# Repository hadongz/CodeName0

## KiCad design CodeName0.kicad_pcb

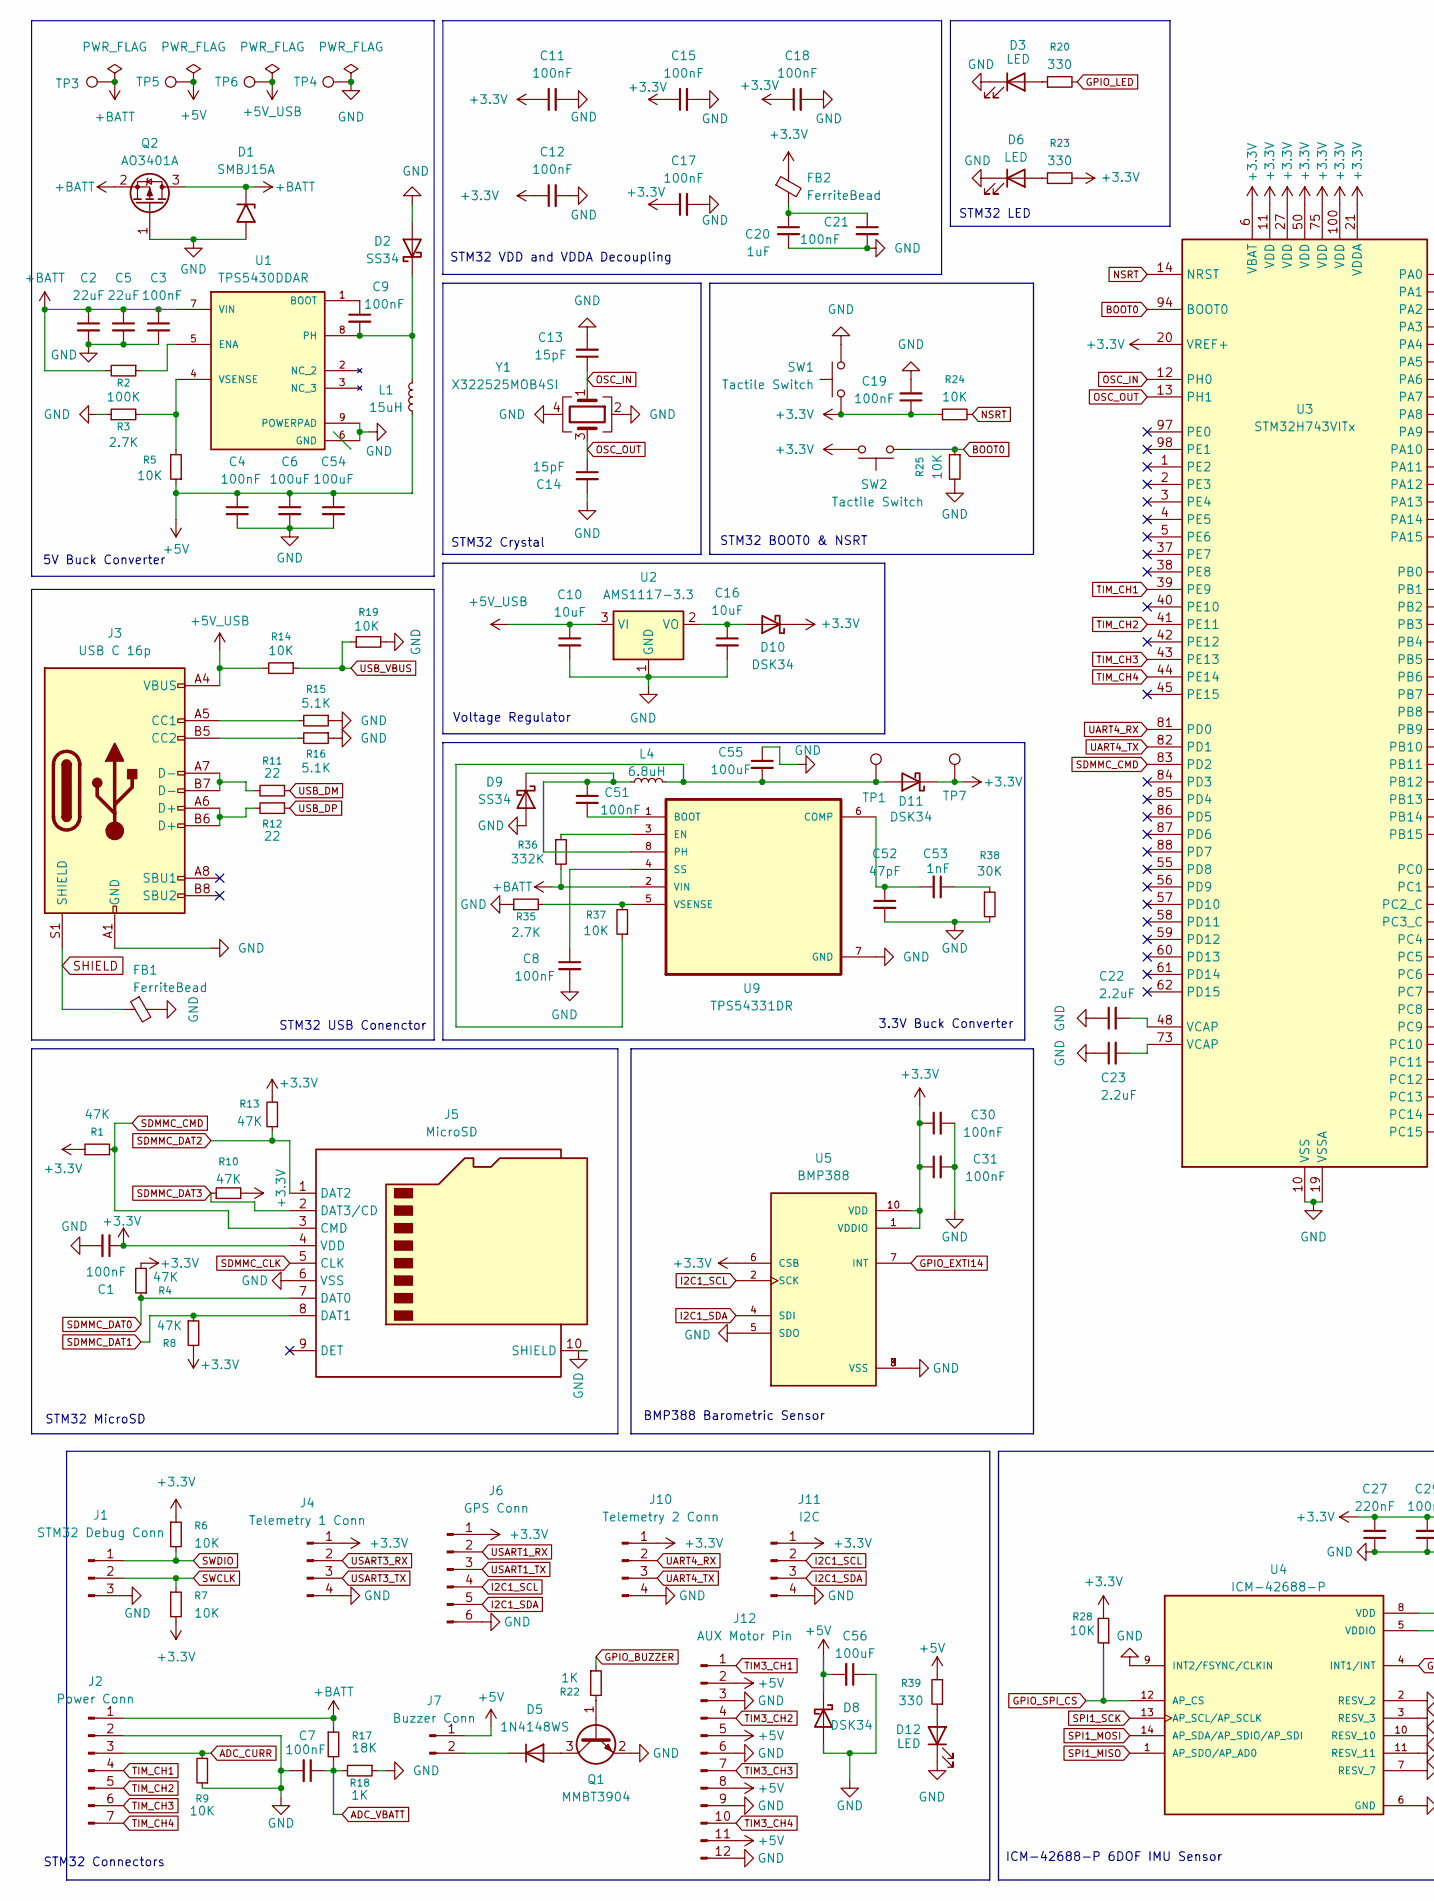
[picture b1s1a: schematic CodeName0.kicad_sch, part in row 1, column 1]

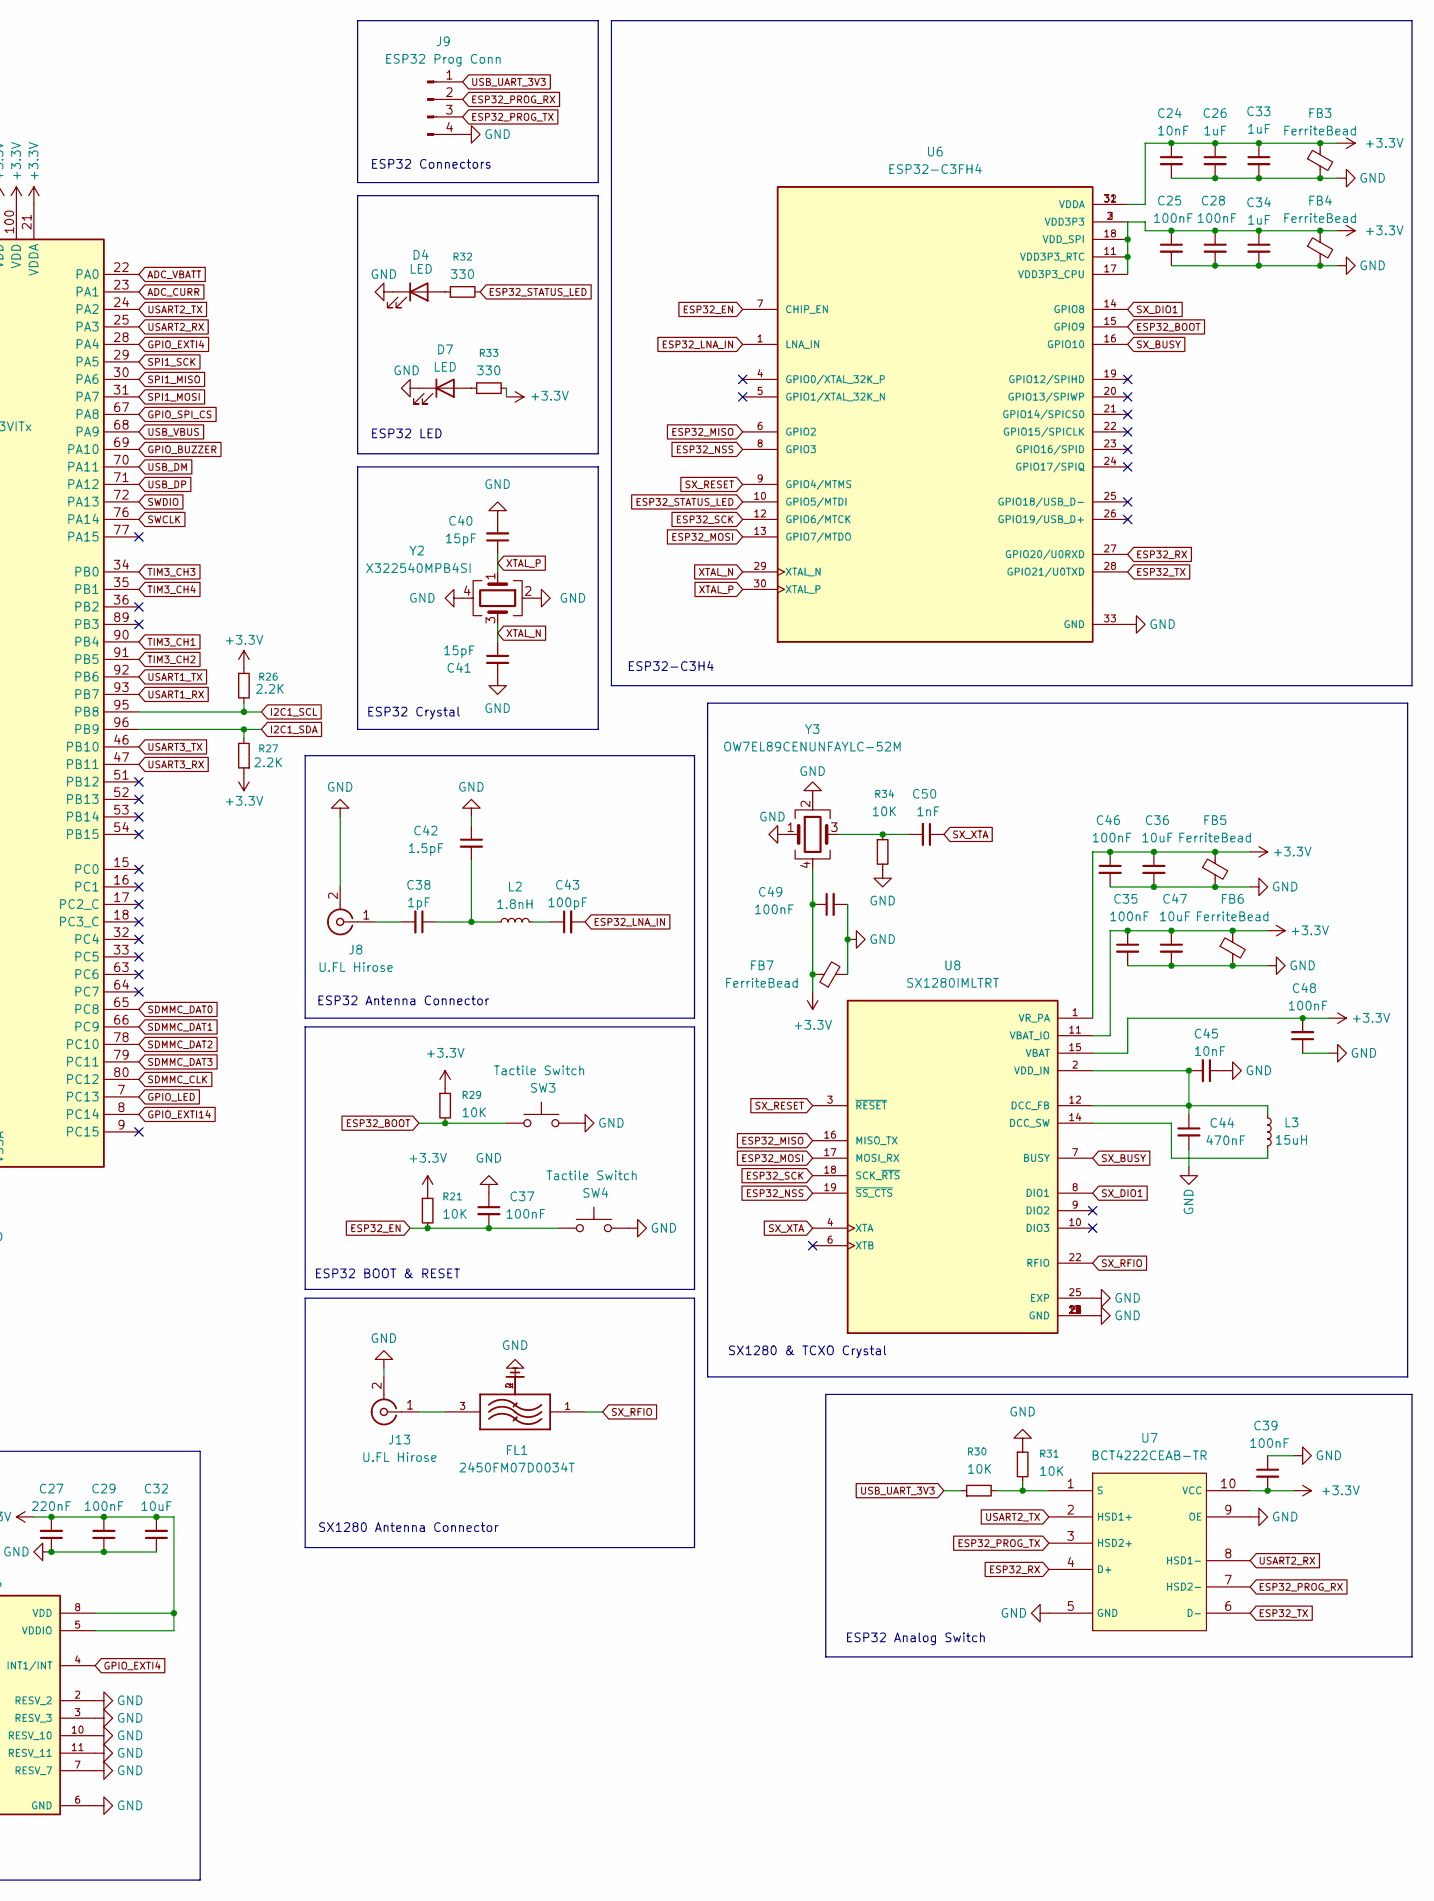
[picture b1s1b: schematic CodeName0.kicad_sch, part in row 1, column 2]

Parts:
C1, C3, C4, C7, C8, C9, C11, C12, C15, C17, C18, C19, C21, C25, C28, C29, C30, C31, C35, C37, C39, C46, C48, C49, C51: 100nF; C_0603_1608Metric
C2, C5: 22uF; C_1206_3216Metric
C6, C54, C55, C56: 100uF; C_1206_3216Metric
C10, C16, C32, C36, C47: 10uF; C_1206_3216Metric
C13, C14, C40, C41: 15pF; C_0603_1608Metric
C20: 1uF; C_0603_1608Metric
C22, C23: 2.2uF; C_0805_2012Metric
C24, C45: 10nF; C_0603_1608Metric
C26, C33, C34: 1uF; C_0805_2012Metric
C27: 220nF; C_0603_1608Metric
C38: 1pF; C_0402_1005Metric
C42: 1.5pF; C_0402_1005Metric
C43: 100pF; C_0402_1005Metric
C44: 470nF; C_0603_1608Metric
C50, C53: 1nF; C_0603_1608Metric
C52: 47pF; C_0402_1005Metric
D1: SMBJ15A; D_SMB
D2, D9: SS34; D_SMA
D3, D4: LED; LED_0805_2012Metric
D5: 1N4148WS; D_SOD-323
D6, D7, D12: LED; LED_0603_1608Metric
D8, D10, D11: DSK34; D_SOD-123F
FB1, FB2, FB3, FB4, FB5, FB6, FB7: FerriteBead; L_0603_1608Metric
FL1: 2450FM07D0034T; FIL_2450FM07D0034T; PARTREV 1.2
J1: STM32 Debug Conn; PinHeader_1x03_P2.54mm_Vertical
J2: Power Conn; JST_GH_SM07B-GHS-TB_1x07-1MP_P1.25mm_Horizontal
J3: USB C 16p; USB_C_Receptacle_HRO_TYPE-C-31-M-12
J4: Telemetry 1 Conn; JST_GH_SM04B-GHS-TB_1x04-1MP_P1.25mm_Horizontal
J5: MicroSD; SUNTECH_ST-TF-003A
J6: GPS Conn; JST_GH_SM06B-GHS-TB_1x06-1MP_P1.25mm_Horizontal
J7: Buzzer Conn; JST_GH_SM02B-GHS-TB_1x02-1MP_P1.25mm_Horizontal
J8, J13: U.FL Hirose; U.FL_Hirose_U.FL-R-SMT-1_Vertical
J9: ESP32 Prog Conn; PinHeader_1x04_P2.54mm_Vertical
J10: Telemetry 2 Conn; JST_GH_SM04B-GHS-TB_1x04-1MP_P1.25mm_Horizontal
J11: I2C; JST_GH_BM04B-GHS-TBT_1x04-1MP_P1.25mm_Vertical
J12: AUX Motor Pin; PinHeader_3x04_P2.54mm_Vertical
L1: 15uH; L_Bourns_SRP7028A_7.3x6.6mm
L2: 1.8nH; L_0402_1005Metric
L3: 15uH; L_Changjiang_FNR3015S
L4: 6.8uH; L_Sunlord_MWSA0503S
Q1: MMBT3904; SOT-23
Q2: AO3401A; SOT-23
R1, R4, R8, R10, R13: 47K; R_0603_1608Metric
R2: 100K; R_0603_1608Metric
R3, R35: 2.7K; R_0603_1608Metric
R5, R6, R7, R9, R14, R19, R21, R24, R25, R28, R29, R30, R31, R34, R37: 10K; R_0603_1608Metric
R11, R12: 22; R_0603_1608Metric
R15, R16: 5.1K; R_0603_1608Metric
R17: 18K; R_0603_1608Metric
R18, R22: 1K; R_0603_1608Metric
R20, R23, R32, R33, R39: 330; R_0603_1608Metric
R26, R27: 2.2K; R_0603_1608Metric
R36: 332K; R_0603_1608Metric
R38: 30K; R_0603_1608Metric
SW1, SW2, SW3, SW4: Tactile Switch; SW_Push_SPST_NO_Alps_SKRK
TP1, TP3, TP5, TP6, TP7: TestPoint; TestPoint_Pad_D1.5mm
TP4: TestPoint; TestPoint_Pad_D2.5mm
U1: TPS5430DDAR; CONV_TPS5430DDAR; PARTREV I
U2: AMS1117-3.3; SOT-223-3_TabPin2
U3: STM32H743VITx; LQFP-100_14x14mm_P0.5mm
U4: ICM-42688-P; PQFN50P300X250X97-14N; PARTREV 1.2
U5: BMP388; PQFN50P200X200X80-10N; PARTREV 1.1
U6: ESP32-C3FH4; QFN50P500X500X90-33N; PARTREV 2.0
U7: BCT4222CEAB-TR; MSOP-10_3x3mm_P0.5mm
U8: SX1280IMLTRT; XCVR_SX1280IMLTRT; PARTREV 3.3
U9: TPS54331DR; SOIC127P599X175-8N
Y1: X322525MOB4SI; Crystal_SMD_3225-4Pin_3.2x2.5mm
Y2: X322540MPB4SI; Crystal_SMD_3225-4Pin_3.2x2.5mm
Y3: OW7EL89CENUNFAYLC-52M; Crystal_SMD_2016-4Pin_2.0x1.6mm

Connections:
+3.3V: C1.1, C11.1, C12.1, C15.1, C17.1, C18.1, C19.1, C24.1, C25.1, C26.1, C27.2, C28.1, C29.2, C30.1, C31.1, C32.2, C33.1, C34.1, C35.1, C36.1, C39.2, C46.1, C47.1, C48.2, C49.1, D10.1 (K), D11.1 (K), FB2.1, FB3.1, FB4.1, FB5.1, FB6.1, FB7.1, J4.1, J5.4 (VDD), J6.1, J10.1, J11.1, R1.1, R4.2, R6.1, R7.2, R8.2, R10.2, R13.2, R21.1, R23.2, R24.1, R26.1, R27.1, R28.2, R29.1, R33.2, SW1.2, SW2.1, TP7.1, U3.6 (VBAT), U3.11 (VDD), U3.20 (VREF+), U3.21 (VDDA), U3.27 (VDD), U3.50 (VDD), U3.75 (VDD), U3.100 (VDD), U4.5 (VDDIO), U4.8 (VDD), U5.1 (VDDIO), U5.6 (CSB), U5.10 (VDD), U6.2 (VDD3P3), U6.3 (VDD3P3), U6.11 (VDD3P3_RTC), U6.17 (VDD3P3_CPU), U6.18 (VDD_SPI), U6.31 (VDDA), U6.32 (VDDA), U7.10 (VCC), U8.1 (VR_PA), U8.11 (VBAT_IO), U8.15 (VBAT), Y3.4
+5V: C4.1, C6.1, C54.1, C56.2, D8.1 (K), J7.1, J12.2, J12.5, J12.8, J12.11, L1.1, R5.1, R39.2, TP5.1
+5V_USB: C10.1, J3.A4 (VBUS), J3.A9 (VBUS), J3.B4 (VBUS), J3.B9 (VBUS), R14.2, TP6.1, U2.3 (VI)
+BATT: C2.1, C3.1, C5.1, D1.1 (A1), J2.1, Q2.2 (S), Q2.3 (D), R2.2, R17.1, R36.2, TP3.1, U1.7 (VIN), U9.2 (VIN)
ADC_CURR: J2.3, R9.2, U3.23 (PA1)
ADC_VBATT: C7.1, R17.2, R18.2, U3.22 (PA0)
BOOT0: R25.1, SW2.2, U3.94 (BOOT0)
ESP32_BOOT: R29.2, SW3.2, U6.15 (GPIO9)
ESP32_EN: C37.2, R21.2, SW4.2, U6.7 (CHIP_EN)
ESP32_LNA_IN: C43.2, U6.1 (LNA_IN)
ESP32_MISO: U6.6 (GPIO2), U8.16 (MISO_TX)
ESP32_MOSI: U6.13 (GPIO7/MTDO), U8.17 (MOSI_RX)
ESP32_NSS: U6.8 (GPIO3), U8.19 (~SS_CTS)
ESP32_PROG_RX: J9.2, U7.7 (HSD2-)
ESP32_PROG_TX: J9.3, U7.3 (HSD2+)
ESP32_RX: U6.27 (GPIO20/U0RXD), U7.4 (D+)
ESP32_SCK: U6.12 (GPIO6/MTCK), U8.18 (SCK_~RTS)
ESP32_STATUS_LED: R32.2, U6.10 (GPIO5/MTDI)
ESP32_TX: U6.28 (GPIO21/U0TXD), U7.6 (D-)
GND: C1.2, C2.2, C3.2, C4.2, C5.2, C6.2, C7.2, C8.2, C10.2, C11.2, C12.2, C13.2, C14.2, C15.2, C16.2, C17.2, C18.2, C19.2, C20.2, C21.2, C22.1, C23.1, C24.2, C25.2, C26.2, C27.1, C28.2, C29.1, C30.2, C31.2, C32.1, C33.2, C34.2, C35.2, C36.2, C37.1, C39.1, C40.2, C41.2, C42.1, C44.2, C45.1, C46.2, C47.2, C48.1, C49.2, C52.2, C54.2, C55.1, C56.1, D1.2 (A2), D2.2 (A), D3.1 (K), D4.1 (K), D6.1 (K), D7.1 (K), D8.2 (A), D9.2 (A), D12.1 (K), FB1.2, FB3.2, FB4.2, FB5.2, FB6.2, FB7.2, FL1.2, FL1.4, J1.3, J2.2, J2.MP, J3.A1 (GND), J3.A12 (GND), J3.B1 (GND), J3.B12 (GND), J4.4, J4.MP, J5.6 (VSS), J5.10 (SHIELD), J6.6, J6.MP, J7.MP, J8.2 (Ext), J9.4, J10.4, J10.MP, J11.4, J11.MP, J12.3, J12.6, J12.9, J12.12, J13.2 (Ext), Q1.2 (E), Q2.1 (G), R3.1, R9.1, R15.1, R16.1, R18.1, R19.2, R25.2, R31.1, R34.2, R35.1, R38.2, SW1.1, SW3.1, SW4.1, TP4.1, U1.6 (GND), U1.9 (POWERPAD), U2.1 (GND), U3.10 (VSS), U3.19 (VSSA), U3.26 (VSS), U3.49 (VSS), U3.74 (VSS), U3.99 (VSS), U4.2 (RESV_2), U4.3 (RESV_3), U4.6 (GND), U4.7 (RESV_7), U4.9 (INT2/FSYNC/CLKIN), U4.10 (RESV_10), U4.11 (RESV_11), U5.3 (VSS), U5.5 (SDO), U5.8 (VSS), U5.9 (VSS), U6.33 (GND), U7.5 (GND), U7.9 (OE), U8.5 (GND), U8.13 (GND), U8.20 (GND), U8.21 (GND), U8.23 (GND), U8.24 (GND), U8.25 (EXP), U9.7 (GND), Y1.2, Y1.4, Y2.2, Y2.4, Y3.1, Y3.2
GPIO_BUZZER: R22.1, U3.69 (PA10)
GPIO_EXTI4: U3.28 (PA4), U4.4 (INT1/INT)
GPIO_EXTI14: U3.8 (PC14), U5.7 (INT)
GPIO_LED: R20.2, U3.7 (PC13)
GPIO_SPI_CS: R28.1, U3.67 (PA8), U4.12 (AP_CS)
I2C1_SCL: J6.4, J11.2, R26.2, U3.95 (PB8), U5.2 (SCK)
I2C1_SDA: J6.5, J11.3, R27.2, U3.96 (PB9), U5.4 (SDI)
NSRT: R24.2, U3.14 (NRST)
unnamed: C20.1, C21.1, FB2.2
unnamed: C22.2, U3.48 (VCAP)
unnamed: C23.2, U3.73 (VCAP)
unnamed: C38.1, C42.2, L2.1
unnamed: C43.1, L2.2
unnamed: C50.2, R34.1, Y3.3
unnamed: C53.1, R38.1
unnamed: C9.2, D2.1 (K), L1.2, U1.8 (PH)
unnamed: D3.2 (A), R20.1
unnamed: D4.2 (A), R32.1
unnamed: D5.2 (A), Q1.3 (C)
unnamed: D5.1 (K), J7.2
unnamed: D6.2 (A), R23.1
unnamed: D7.2 (A), R33.1
unnamed: C51.1, D9.1 (K), L4.1, U9.8 (PH)
unnamed: C16.1, D10.2 (A), U2.2 (VO)
unnamed: C55.2, D11.2 (A), L4.2, R37.1, TP1.1
unnamed: D12.2 (A), R39.1
unnamed: J3.A5 (CC1), R15.2
unnamed: J3.B5 (CC2), R16.2
unnamed: J3.A6 (D+), J3.B6 (D+), R12.2
unnamed: J3.A7 (D-), J3.B7 (D-), R11.2
unnamed: C38.2, J8.1 (In)
unnamed: FL1.3, J13.1 (In)
unnamed: Q1.1 (B), R22.2
unnamed: C9.1, U1.1 (BOOT)
unnamed: R2.1, U1.5 (ENA)
unnamed: R3.2, R5.2, U1.4 (VSENSE)
unnamed: R30.2, R31.2, U7.1 (S)
unnamed: C44.1, C45.2, L3.1, U8.2 (VDD_IN), U8.12 (DCC_FB)
unnamed: L3.2, U8.14 (DCC_SW)
unnamed: C51.2, U9.1 (BOOT)
unnamed: C52.1, C53.2, U9.6 (COMP)
unnamed: R36.1, U9.3 (EN)
unnamed: C8.1, U9.4 (SS)
unnamed: R35.2, R37.2, U9.5 (VSENSE)
OSC_IN: C13.1, U3.12 (PH0), Y1.1
OSC_OUT: C14.1, U3.13 (PH1), Y1.3
SDMMC_CLK: J5.5 (CLK), U3.80 (PC12)
SDMMC_CMD: J5.3 (CMD), R1.2, U3.83 (PD2)
SDMMC_DAT0: J5.7 (DAT0), R4.1, U3.65 (PC8)
SDMMC_DAT1: J5.8 (DAT1), R8.1, U3.66 (PC9)
SDMMC_DAT2: J5.1 (DAT2), R13.1, U3.78 (PC10)
SDMMC_DAT3: J5.2 (DAT3/CD), R10.1, U3.79 (PC11)
SHIELD: FB1.1, J3.S1 (SHIELD)
SPI1_MISO: U3.30 (PA6), U4.1 (AP_SDO/AP_AD0)
SPI1_MOSI: U3.31 (PA7), U4.14 (AP_SDA/AP_SDIO/AP_SDI)
SPI1_SCK: U3.29 (PA5), U4.13 (AP_SCL/AP_SCLK)
SWCLK: J1.2, R7.1, U3.76 (PA14)
SWDIO: J1.1, R6.2, U3.72 (PA13)
SX_BUSY: U6.16 (GPIO10), U8.7 (BUSY)
SX_DIO1: U6.14 (GPIO8), U8.8 (DIO1)
SX_RESET: U6.9 (GPIO4/MTMS), U8.3 (~RESET)
SX_RFIO: FL1.1, U8.22 (RFIO)
SX_XTA: C50.1, U8.4 (XTA)
TIM3_CH1: J12.1, U3.90 (PB4)
TIM3_CH2: J12.4, U3.91 (PB5)
TIM3_CH3: J12.7, U3.34 (PB0)
TIM3_CH4: J12.10, U3.35 (PB1)
TIM_CH1: J2.4, U3.39 (PE9)
TIM_CH2: J2.5, U3.41 (PE11)
TIM_CH3: J2.6, U3.43 (PE13)
TIM_CH4: J2.7, U3.44 (PE14)
UART4_RX: J10.2, U3.81 (PD0)
UART4_TX: J10.3, U3.82 (PD1)
USART1_RX: J6.2, U3.93 (PB7)
USART1_TX: J6.3, U3.92 (PB6)
USART2_RX: U3.25 (PA3), U7.8 (HSD1-)
USART2_TX: U3.24 (PA2), U7.2 (HSD1+)
USART3_RX: J4.2, U3.47 (PB11)
USART3_TX: J4.3, U3.46 (PB10)
USB_DM: R11.1, U3.70 (PA11)
USB_DP: R12.1, U3.71 (PA12)
USB_UART_3V3: J9.1, R30.1
USB_VBUS: R14.1, R19.1, U3.68 (PA9)
XTAL_N: C41.1, U6.29 (XTAL_N), Y2.3
XTAL_P: C40.1, U6.30 (XTAL_P), Y2.1

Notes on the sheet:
STM32 Crystal
ESP32 Connectors
ESP32-C3H4
SX1280 & TCXO Crystal
STM32 LED
STM32 BOOT0 & NSRT
ESP32 Analog Switch
STM32 VDD and VDDA Decoupling
STM32 USB Conenctor
STM32 Connectors
SX1280 Antenna Connector
STM32 MicroSD
BMP388 Barometric Sensor
ICM-42688-P 6DOF IMU Sensor
ESP32 LED
ESP32 Antenna Connector
3.3V Buck Converter
Voltage Regulator
5V Buck Converter
ESP32 Crystal
ESP32 BOOT & RESET

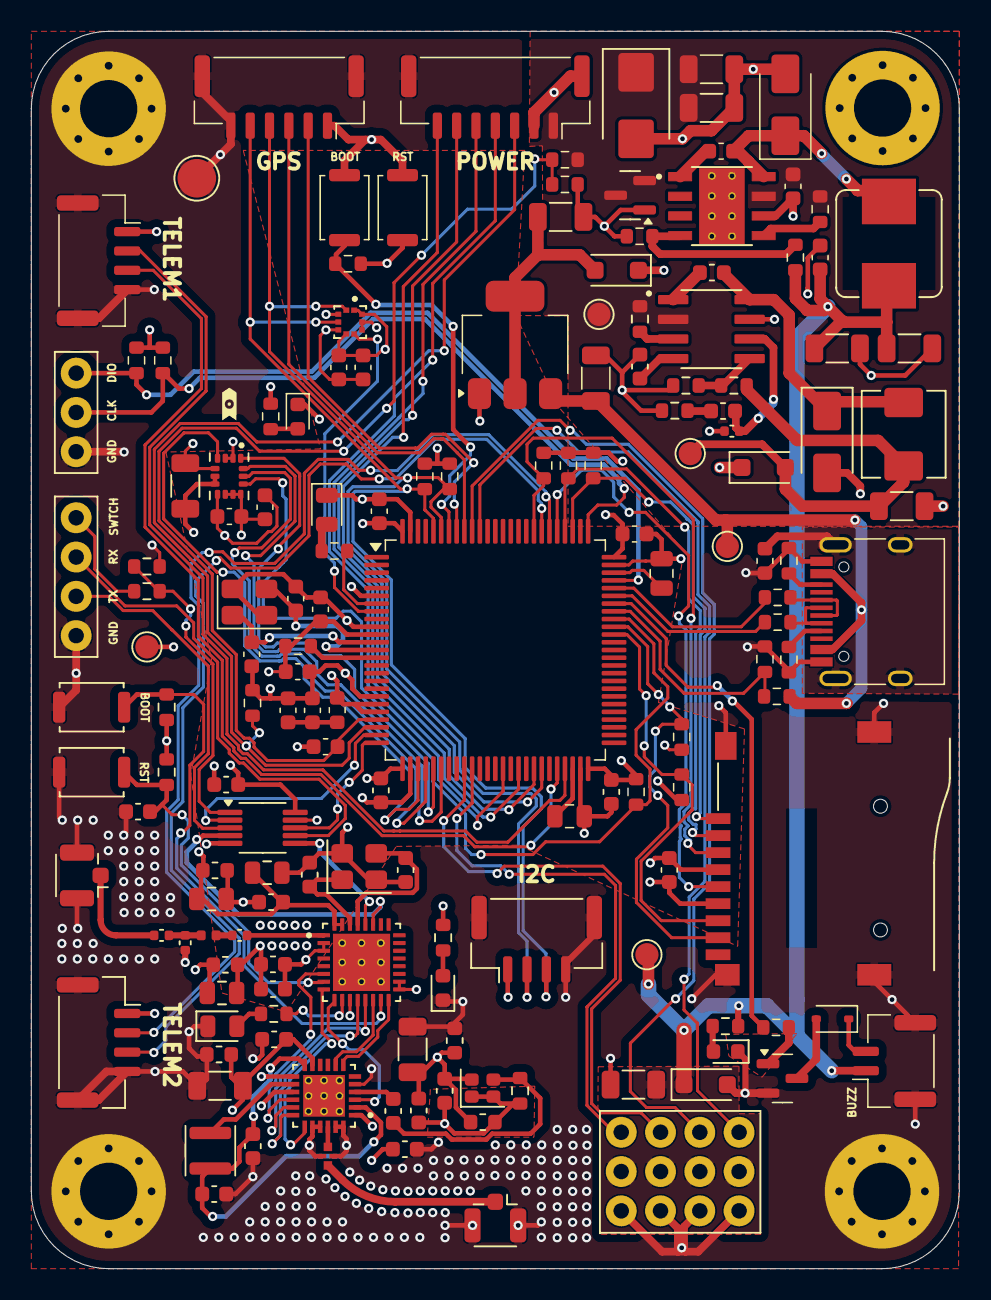
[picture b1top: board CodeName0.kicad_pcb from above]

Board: 4 copper layers, 60.0 x 80.0 mm, 157 parts (0 on the bottom side), 105 nets.

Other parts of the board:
kibuzzard-68C3DDBA: G***; kibuzzard-68C3DDBA

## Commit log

2025-09-07 feat: initial commit
2025-09-12 feat: layouting PCB
2025-09-12 fix: DRC warnings
2025-09-12 feat: remove esp32-c3 wroom
2025-09-14 feat: ESP32-C3 schematic and pcb layout
2025-09-14 feat: SX1280
2025-09-16 feat: redesign power archtecture and integrate SX1280
2025-09-16 feat: polishing and finishing
